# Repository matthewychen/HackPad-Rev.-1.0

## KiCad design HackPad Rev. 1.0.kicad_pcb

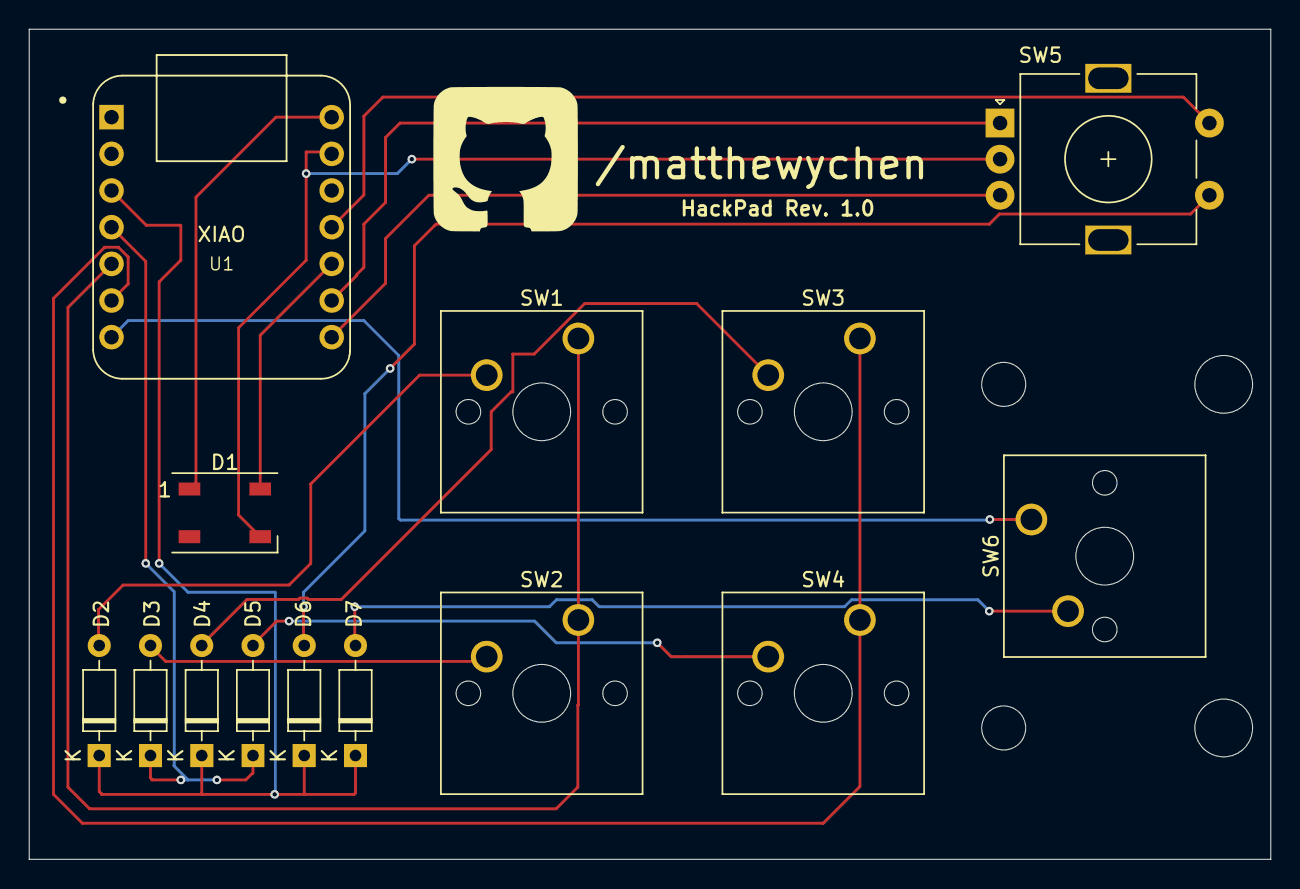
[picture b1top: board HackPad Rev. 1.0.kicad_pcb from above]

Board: 2 copper layers, 86.0 x 57.5 mm, 14 parts (0 on the bottom side), 17 nets.

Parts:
D1: WS2812B; LED_WS2812B_PLCC4_5.0x5.0mm_P3.2mm
D2, D3, D4, D5, D6, D7: D; D_DO-35_SOD27_P7.62mm_Horizontal
SW1, SW2, SW3, SW4: SW_Push_45deg; SW_Cherry_MX_1.00u_PCB
SW5: RotaryEncoder_Switch; RotaryEncoder_Alps_EC11E-Switch_Vertical_H20mm
SW6: SW_Push_45deg; SW_Cherry_MX_2.00u_PCB
U1: Seeed Studio XIAO SAMD21; XIAO-Generic-Thruhole-14P-2.54-21X17.8MM

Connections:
/C0: SW1.1, SW2.1, U1.5 (PA8_A4_D4_SDA)
/C2: SW3.1, SW4.1, U1.6 (PA9_A5_D5_SCL)
GND: D1.3 (VSS), SW5.C, U1.13 (GND)
unnamed: D1.4 (DIN), U1.10 (PA5_A9_D9_MISO)
unnamed: D2.2 (A), SW1.2
unnamed: D2.1 (K), D4.1 (K), D6.1 (K), D7.1 (K), U1.3 (PA10_A2_D2)
unnamed: D3.2 (A), SW2.2
unnamed: D3.1 (K), D5.1 (K), U1.4 (PA11_A3_D3)
unnamed: D4.2 (A), SW3.2
unnamed: D5.2 (A), SW4.2
unnamed: D6.2 (A), SW5.S1
unnamed: D7.2 (A), SW6.2
unnamed: SW5.S2, U1.11 (PA6_A10_D10_MOSI)
unnamed: SW5.A, U1.9 (PA7_A8_D8_SCK)
unnamed: SW6.1, U1.7 (PB08_A6_D6_TX)
unnamed: SW5.B, U1.8 (PB09_A7_D7_RX)
VCC: D1.1 (VDD), U1.14 (5V)

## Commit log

2024-10-10 Initial commit with PCB layout
2024-10-10 finished PCB
2024-10-12 finished 3d model
